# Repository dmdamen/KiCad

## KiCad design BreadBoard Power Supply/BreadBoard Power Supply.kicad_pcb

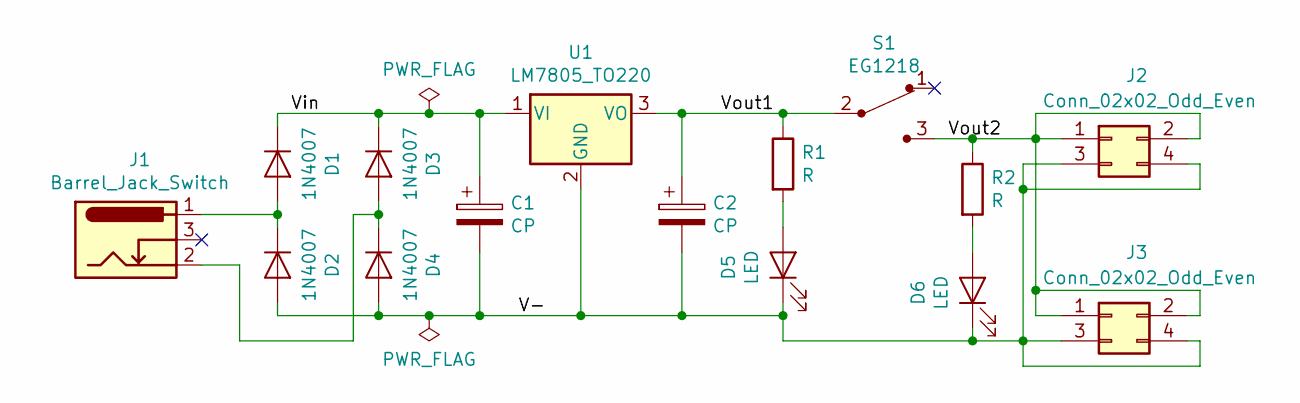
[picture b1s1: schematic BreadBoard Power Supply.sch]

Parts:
C1: CP; CP_Radial_D10.0mm_P5.00mm
C2: CP; CP_Radial_D6.3mm_P2.50mm
D1, D2, D3, D4: 1N4007; D_DO-41_SOD81_P10.16mm_Horizontal
D5, D6: LED; LED_D5.0mm_Clear
J1: Barrel_Jack_Switch; BarrelJack_Horizontal
J2, J3: Conn_02x02_Odd_Even; PinHeader_2x02_P2.54mm_Vertical
R1, R2: R; R_Axial_DIN0207_L6.3mm_D2.5mm_P7.62mm_Horizontal
S1: EG1218; Switch_Slide_11.6x4mm_EG1218; MPN EG1218; Digi-Key_PN EG1903-ND
U1: LM7805_TO220; TO-220-3_Vertical

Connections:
/V-: C1.2, C2.2, D2.2 (A), D4.2 (A), D5.1 (K), D6.1 (K), J2.3, J2.4, J3.3, J3.4, U1.2 (GND)
/Vin: C1.1, D1.1 (K), D3.1 (K), U1.1 (VI)
/Vout1: C2.1, R1.1, S1.2, U1.3 (VO)
/Vout2: J2.1, J2.2, J3.1, J3.2, R2.1, S1.3
unnamed: D1.2 (A), D2.1 (K), J1.1
unnamed: D3.2 (A), D4.1 (K), J1.2
unnamed: D5.2 (A), R1.2
unnamed: D6.2 (A), R2.2

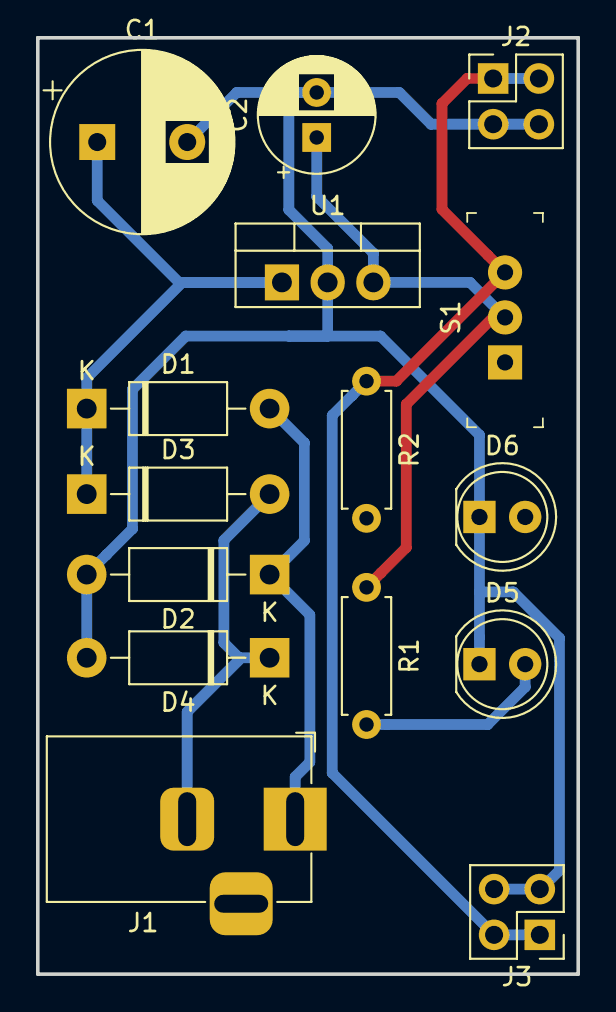
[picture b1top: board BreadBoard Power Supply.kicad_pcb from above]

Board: 2 copper layers, 30.0 x 52.0 mm, 15 parts (0 on the bottom side), 8 nets.

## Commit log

2019-02-23 Test Git
2019-02-23 Test Git 2
2019-02-23 Initial Projects commits
